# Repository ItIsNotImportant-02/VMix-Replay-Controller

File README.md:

# vMix Replay Controller

Vlastní hardwarový ovladač pro vMix Replay ve stylu EVS: RGB tlačítka, páka pro rychlost, jog kolečko. Vlastní PCB (KiCad, osazení JLCPCB), vlastní firmware, 3D tištěná krabička.

- Plán projektu: [docs/PLAN.md](docs/PLAN.md)
- Dashboard postupu: https://claude.ai/artifact/F6eHfhQ5NSxDFNfWmzDA3g
- Deep Research prompty: [docs/research/](docs/research/)

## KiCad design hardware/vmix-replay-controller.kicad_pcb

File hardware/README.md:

# Hardware (KiCad 9)

Hlavní deska ovladače. Popis návrhu a otevřené body: [DESIGN.md](DESIGN.md), piny a mapování tlačítek/LED: [PINMAP.md](PINMAP.md).

- `vmix-replay-controller.kicad_pro` a `vmix-replay-controller.kicad_sch`: projekt a jednostránkové blokové schéma (generované z `tools/circuit.py` + `tools/layout.py`, needitovat ručně)
- `lib/`: vlastní symboly a footprinty (PB26, TS5, IS31FL3236A QFN-44)
- `tools/`: generátor schématu a footprintů (`gen.py`), kontrola netlistu (`verify.py`), rozmístění desky ze schématu (`pcb.py`) a export BOM + CPL pro JLCPCB (`jlc.py`)
- `production/`: výrobní data pro JLCPCB (Gerber, BOM, CPL), doplní se po návrhu desky

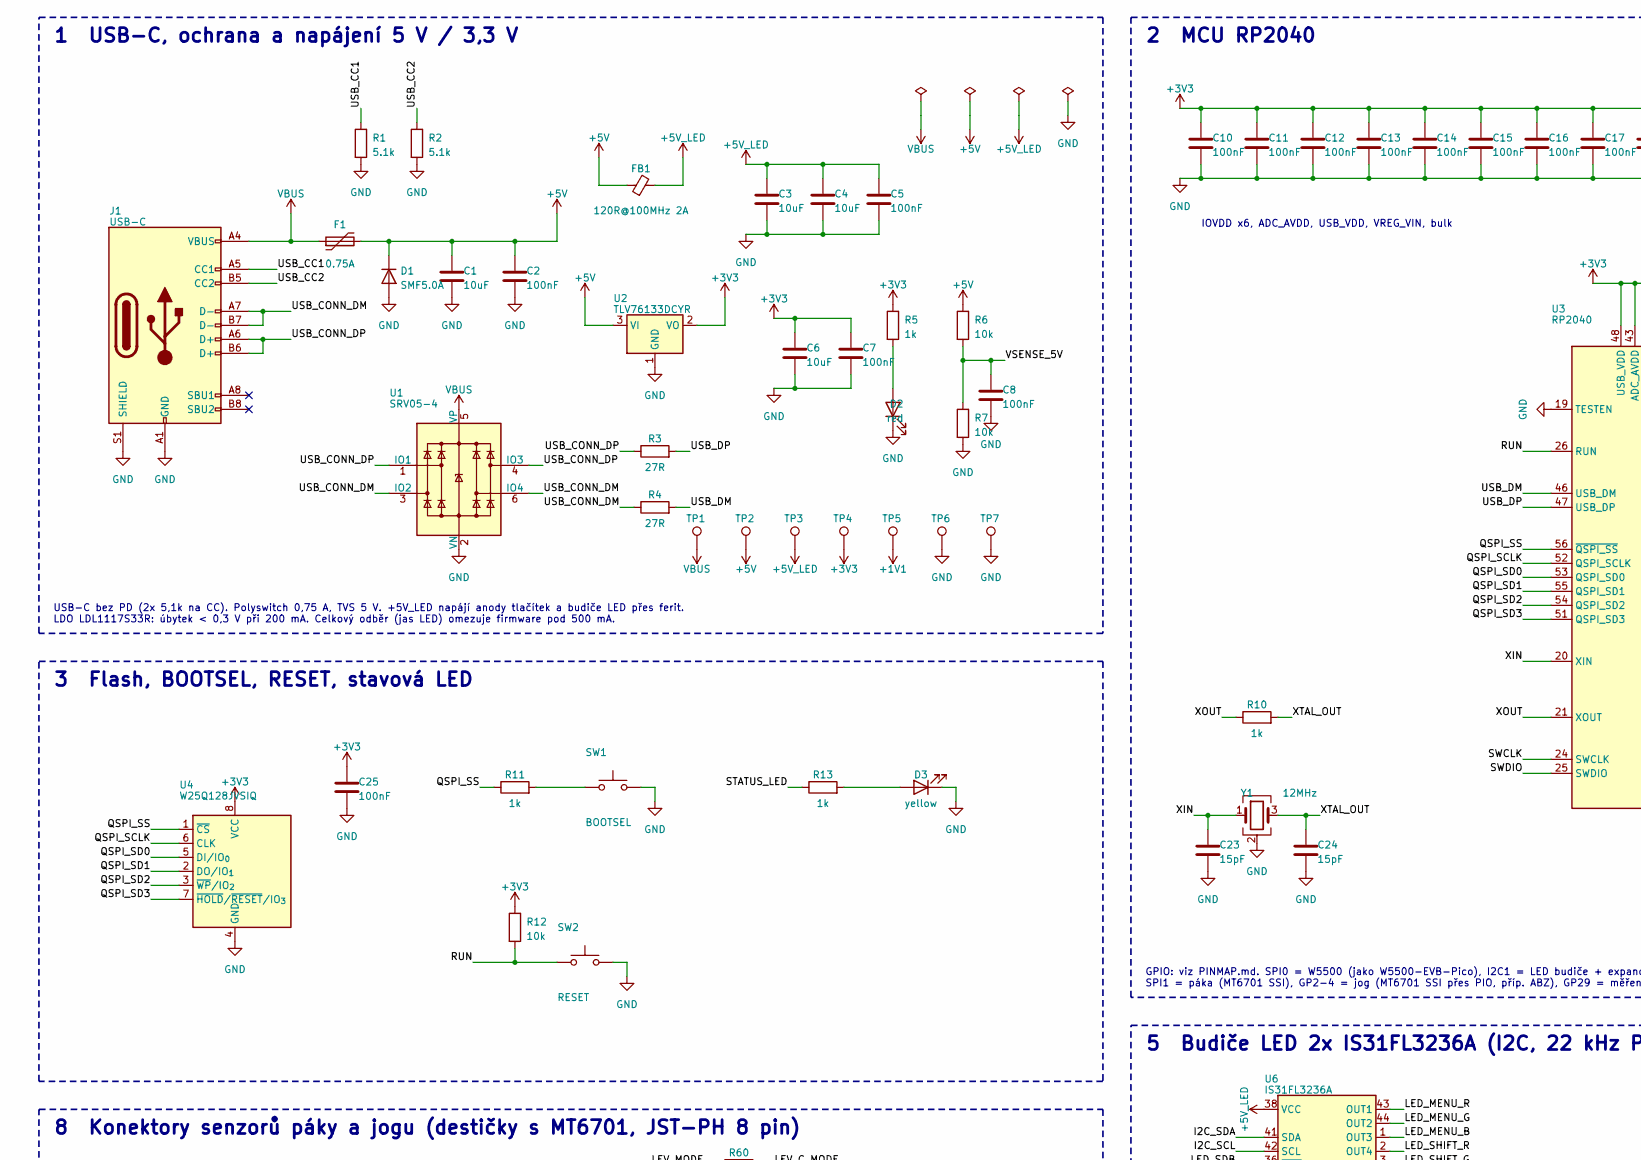
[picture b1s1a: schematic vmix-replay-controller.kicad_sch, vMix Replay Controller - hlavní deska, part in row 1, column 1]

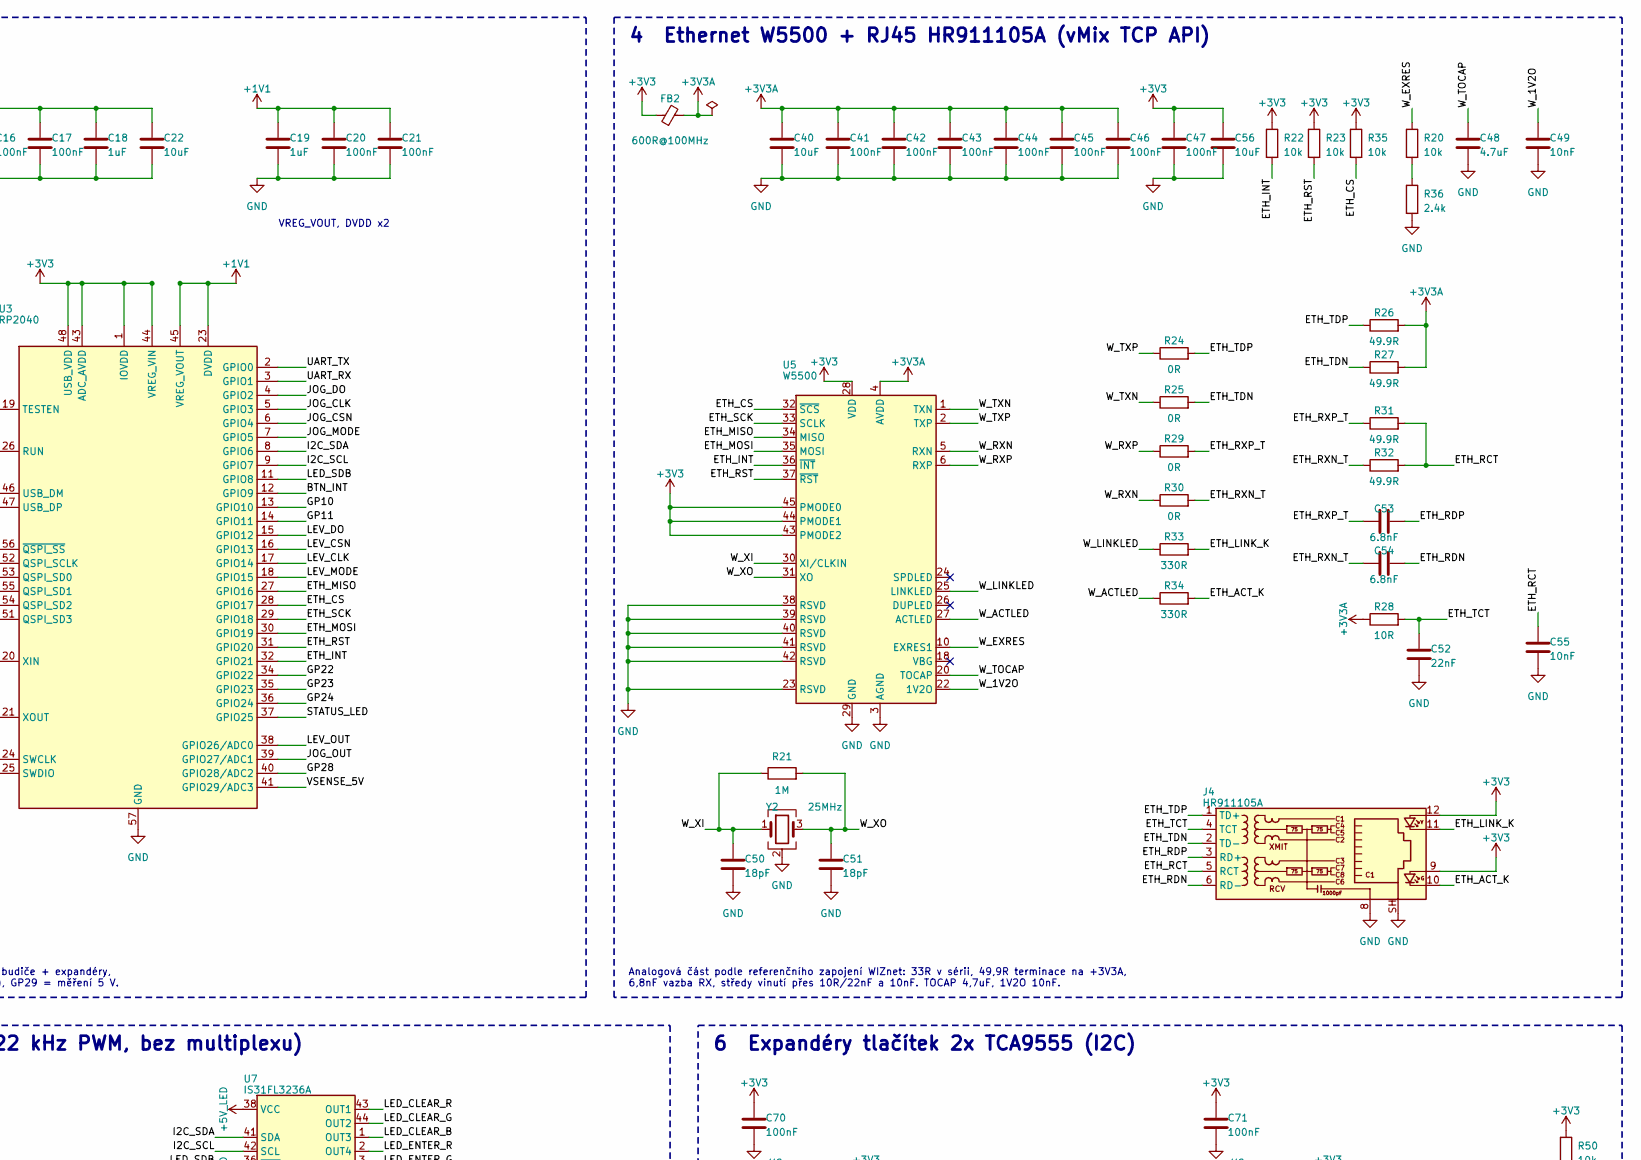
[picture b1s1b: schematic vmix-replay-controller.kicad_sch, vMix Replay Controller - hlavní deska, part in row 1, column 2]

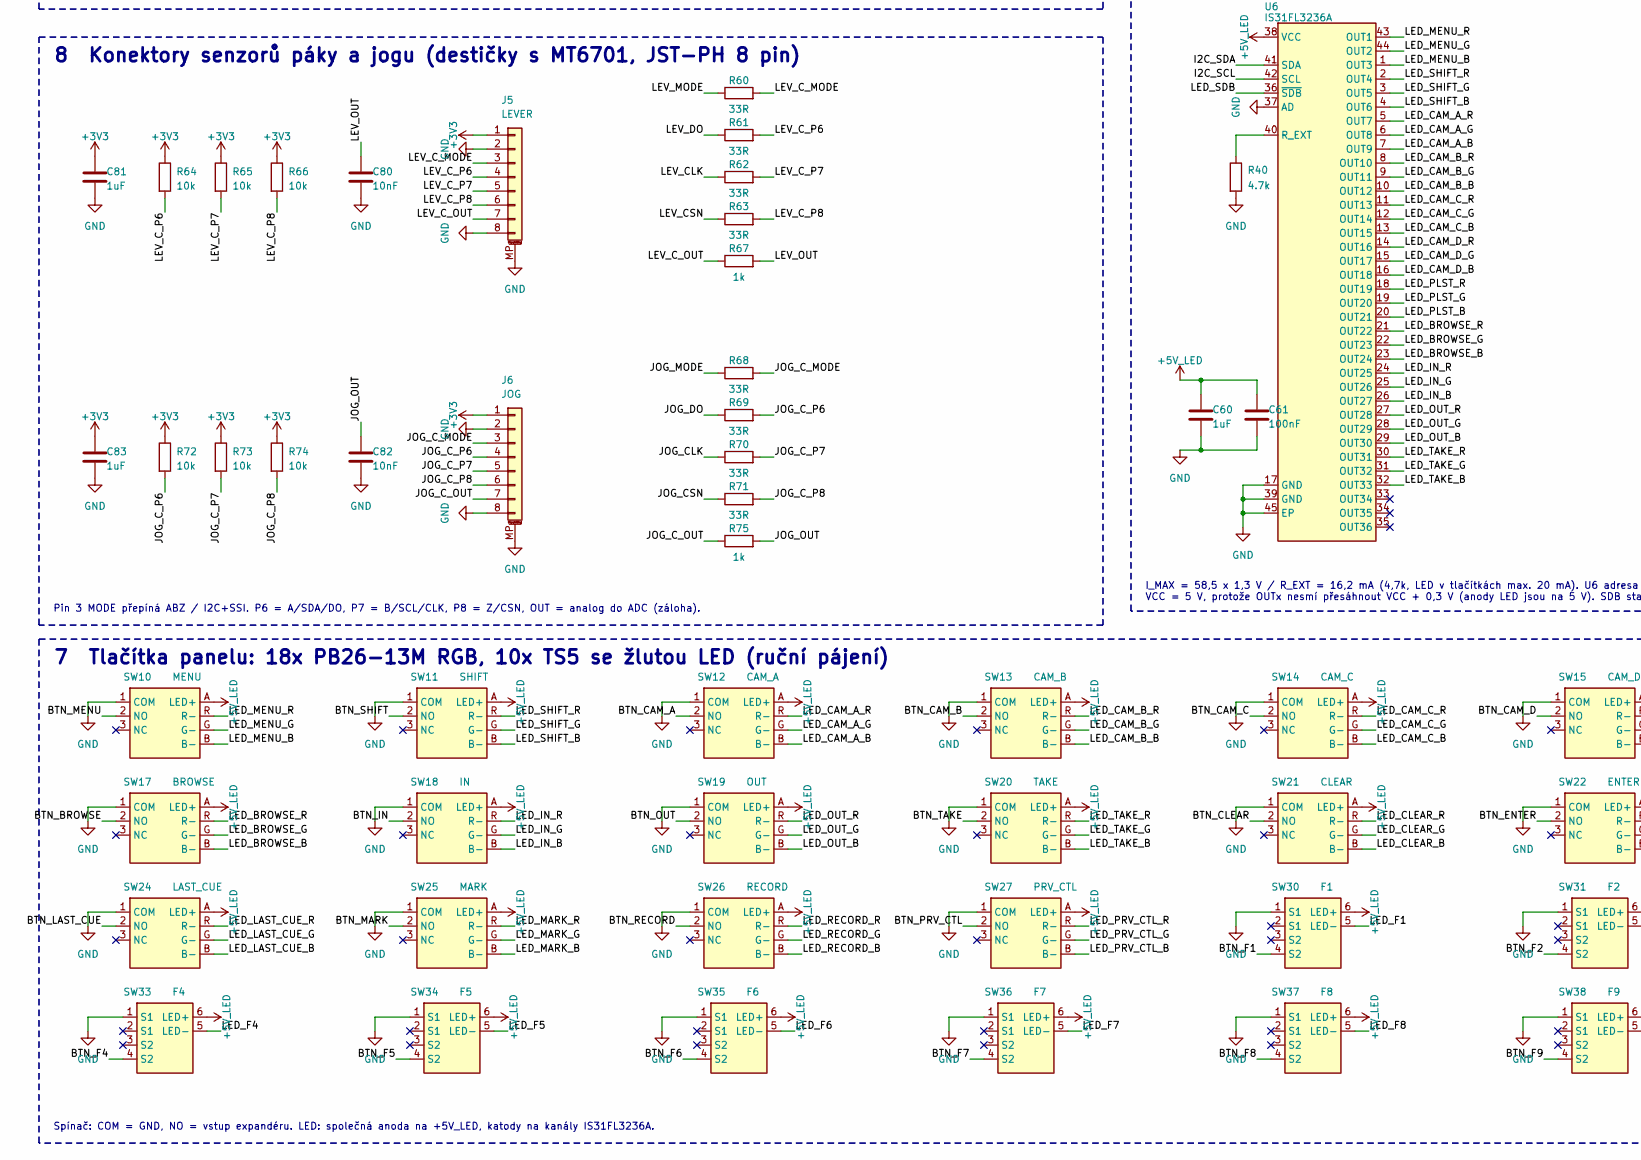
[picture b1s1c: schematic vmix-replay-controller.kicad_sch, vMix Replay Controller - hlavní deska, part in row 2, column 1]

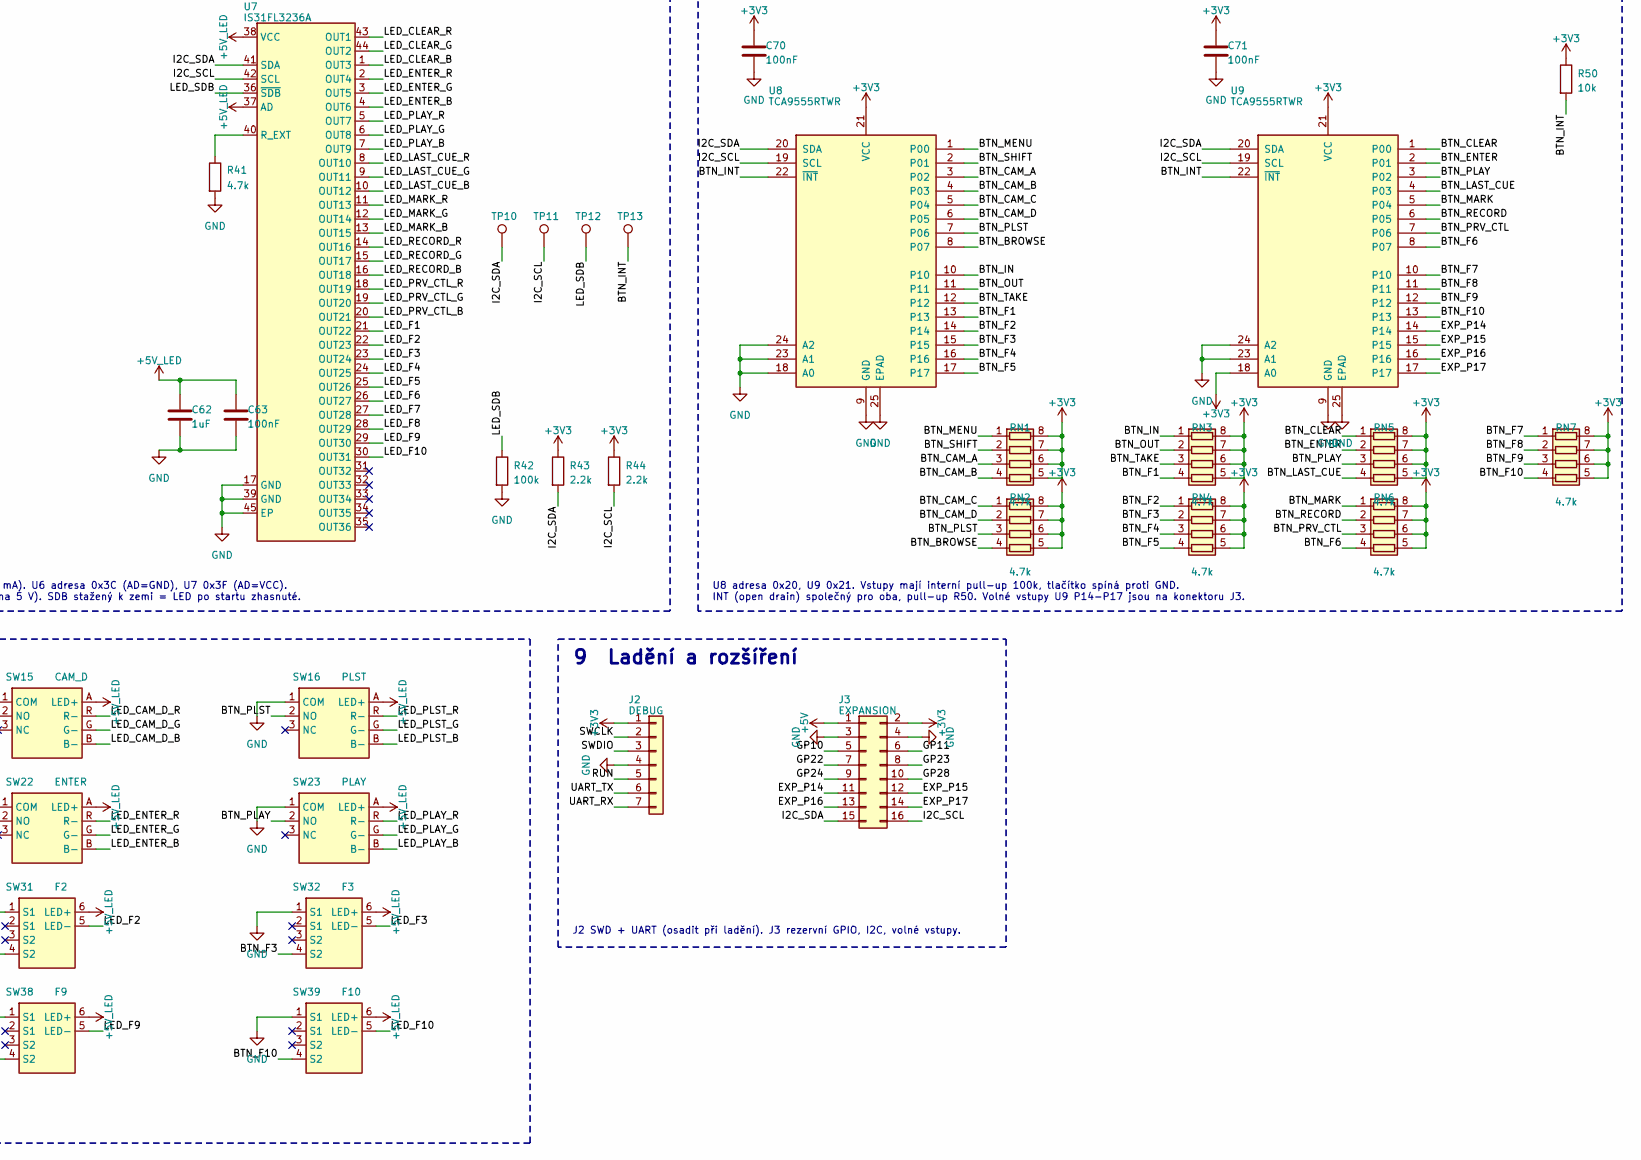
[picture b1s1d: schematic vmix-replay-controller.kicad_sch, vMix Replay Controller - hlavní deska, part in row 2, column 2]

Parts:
C1, C3, C4, C6, C22, C40, C56: 10uF; C_0805_2012Metric; LCSC C15850
C2, C5, C7, C8, C10, C11, C12, C13, C14, C15, C16, C17, C20, C21, C25, C41, C42, C43, C44, C45, C46, C47, C61, C63, C70, C71: 100nF; C_0603_1608Metric; LCSC C14663
C18, C19, C60, C62, C81, C83: 1uF; C_0603_1608Metric; LCSC C15849
C23, C24: 15pF; C_0603_1608Metric; LCSC C1644
C48: 4.7uF; C_0603_1608Metric; LCSC C19666
C49, C55, C80, C82: 10nF; C_0603_1608Metric; LCSC C57112
C50, C51: 18pF; C_0603_1608Metric; LCSC C1647
C52: 22nF; C_0603_1608Metric; LCSC C21122
C53, C54: 6.8nF; C_0603_1608Metric; LCSC C1631
D1: SMF5.0A; D_SOD-123F; MPN hongjiacheng SMF5.0A; LCSC C19077497
D2: red; LED_0603_1608Metric; MPN KENTO KT-0603R; LCSC C2286
D3: yellow; LED_0603_1608Metric; MPN NationStar NCD0603Y2; LCSC C89811
F1: 0.75A; Fuse_1206_3216Metric; MPN JK-nSMD075/6V; LCSC C2830242
FB1: 120R@100MHz 2A; L_0603_1608Metric; MPN BLM18PG121SN1D; LCSC C14709
FB2: 600R@100MHz; L_0805_2012Metric; LCSC C1017
J1: USB-C; USB_C_Receptacle_HRO_TYPE-C-31-M-12; MPN TYPE-C-31-M-12; LCSC C165948
J2: DEBUG; PinHeader_1x07_P2.54mm_Vertical
J3: EXPANSION; PinHeader_2x08_P2.54mm_Vertical
J4: HR911105A; RJ45_Hanrun_HR911105A_Horizontal; LCSC C12074
J5: LEVER; JST_PH_S8B-PH-SM4-TB_1x08-1MP_P2.00mm_Horizontal; MPN S8B-PH-SM4-TB; LCSC C265121
J6: JOG; JST_PH_S8B-PH-SM4-TB_1x08-1MP_P2.00mm_Horizontal; MPN S8B-PH-SM4-TB; LCSC C265121
R1, R2: 5.1k; R_0603_1608Metric; Tolerance 1%; LCSC C23186
R3, R4: 27R; R_0603_1608Metric; Tolerance 1%; LCSC C25190
R5, R10, R11, R13, R67, R75: 1k; R_0603_1608Metric; Tolerance 1%; LCSC C21190
R6, R7, R12, R20, R22, R23, R35, R50, R64, R65, R66, R72, R73, R74: 10k; R_0603_1608Metric; Tolerance 1%; LCSC C25804
R21: 1M; R_0603_1608Metric; Tolerance 1%; LCSC C22935
R24, R25, R29, R30: 0R; R_0603_1608Metric; Tolerance 1%; LCSC C21189
R26, R27, R31, R32: 49.9R; R_0603_1608Metric; Tolerance 1%; LCSC C23185
R28: 10R; R_0603_1608Metric; Tolerance 1%; LCSC C22859
R33, R34: 330R; R_0603_1608Metric; Tolerance 1%; LCSC C23138
R36: 2.4k; R_0603_1608Metric; Tolerance 1%; LCSC C22940
R40, R41: 4.7k; R_0603_1608Metric; Tolerance 1%; LCSC C23162
R42: 100k; R_0603_1608Metric; Tolerance 1%; LCSC C25803
R43, R44: 2.2k; R_0603_1608Metric; Tolerance 1%; LCSC C4190
R60, R61, R62, R63, R68, R69, R70, R71: 33R; R_0603_1608Metric; Tolerance 1%; LCSC C23140
RN1, RN2, RN3, RN4, RN5, RN6, RN7: 4.7k; R_Array_Convex_4x0603; MPN 4D03WGJ0472T5E; LCSC C1980
SW1: BOOTSEL; SW_Push_1P1T_XKB_TS-1187A; LCSC C318884
SW2: RESET; SW_Push_1P1T_XKB_TS-1187A; LCSC C318884
SW10: MENU; PB26-13M-RGB; MPN PB26-13M-B-WT-RGB-N
SW11: SHIFT; PB26-13M-RGB; MPN PB26-13M-B-WT-RGB-N
SW12: CAM_A; PB26-13M-RGB; MPN PB26-13M-B-WT-RGB-N
SW13: CAM_B; PB26-13M-RGB; MPN PB26-13M-B-WT-RGB-N
SW14: CAM_C; PB26-13M-RGB; MPN PB26-13M-B-WT-RGB-N
SW15: CAM_D; PB26-13M-RGB; MPN PB26-13M-B-WT-RGB-N
SW16: PLST; PB26-13M-RGB; MPN PB26-13M-B-WT-RGB-N
SW17: BROWSE; PB26-13M-RGB; MPN PB26-13M-B-WT-RGB-N
SW18: IN; PB26-13M-RGB; MPN PB26-13M-B-WT-RGB-N
SW19: OUT; PB26-13M-RGB; MPN PB26-13M-B-WT-RGB-N
SW20: TAKE; PB26-13M-RGB; MPN PB26-13M-B-WT-RGB-N
SW21: CLEAR; PB26-13M-RGB; MPN PB26-13M-B-WT-RGB-N
SW22: ENTER; PB26-13M-RGB; MPN PB26-13M-B-WT-RGB-N
SW23: PLAY; PB26-13M-RGB; MPN PB26-13M-B-WT-RGB-N
SW24: LAST_CUE; PB26-13M-RGB; MPN PB26-13M-B-WT-RGB-N
SW25: MARK; PB26-13M-RGB; MPN PB26-13M-B-WT-RGB-N
SW26: RECORD; PB26-13M-RGB; MPN PB26-13M-B-WT-RGB-N
SW27: PRV_CTL; PB26-13M-RGB; MPN PB26-13M-B-WT-RGB-N
SW30: F1; TS5-9.2mm-LED; MPN TS5 yellow
SW31: F2; TS5-9.2mm-LED; MPN TS5 yellow
SW32: F3; TS5-9.2mm-LED; MPN TS5 yellow
SW33: F4; TS5-9.2mm-LED; MPN TS5 yellow
SW34: F5; TS5-9.2mm-LED; MPN TS5 yellow
SW35: F6; TS5-9.2mm-LED; MPN TS5 yellow
SW36: F7; TS5-9.2mm-LED; MPN TS5 yellow
SW37: F8; TS5-9.2mm-LED; MPN TS5 yellow
SW38: F9; TS5-9.2mm-LED; MPN TS5 yellow
SW39: F10; TS5-9.2mm-LED; MPN TS5 yellow
TP1: VBUS; TestPoint_Pad_D1.5mm
TP2: +5V; TestPoint_Pad_D1.5mm
TP3: +5V_LED; TestPoint_Pad_D1.5mm
TP4: +3V3; TestPoint_Pad_D1.5mm
TP5: +1V1; TestPoint_Pad_D1.5mm
TP6, TP7: GND; TestPoint_Pad_D1.5mm
TP10: I2C_SDA; TestPoint_Pad_D1.5mm
TP11: I2C_SCL; TestPoint_Pad_D1.5mm
TP12: LED_SDB; TestPoint_Pad_D1.5mm
TP13: BTN_INT; TestPoint_Pad_D1.5mm
U1: SRV05-4; SOT-23-6; MPN hongjiacheng SRV05-4; LCSC C7420376
U2: TLV76133DCYR; SOT-223-3_TabPin2; MPN TLV76133DCYR; LCSC C7527500
U3: RP2040; QFN-56-1EP_7x7mm_P0.4mm_EP3.2x3.2mm; LCSC C2040
U4: W25Q128JVSIQ; SOIC-8_5.3x5.3mm_P1.27mm; LCSC C97521
U5: W5500; LQFP-48_7x7mm_P0.5mm; LCSC C32843
U6, U7: IS31FL3236A; QFN-44-1EP_5x5mm_P0.4mm; MPN IS31FL3236A-QFLS2-TR; LCSC C246443
U8, U9: TCA9555RTWR; Texas_RTW_WQFN-24-1EP_4x4mm_P0.5mm_EP2.7x2.7mm; LCSC C140277
Y1: 12MHz; Crystal_SMD_3225-4Pin_3.2x2.5mm; MPN TX322512M4DBDE2T; LCSC C5310728
Y2: 25MHz; Crystal_SMD_3225-4Pin_3.2x2.5mm; MPN X322525MOB4SI (CL 12 pF); LCSC C9006

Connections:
+1V1: C19.1, C20.1, C21.1, TP5.1, U3.23 (DVDD), U3.45 (VREG_VOUT), U3.50 (DVDD)
+3V3: C6.1, C7.1, C10.1, C11.1, C12.1, C13.1, C14.1, C15.1, C16.1, C17.1, C18.1, C22.1, C25.1, C47.1, C56.1, C70.1, C71.1, C81.1, C83.1, FB2.1, J2.1, J3.2, J4.9, J4.12, J5.1, J6.1, R5.1, R12.1, R22.1, R23.1, R35.1, R43.1, R44.1, R50.1, R64.1, R65.1, R66.1, R72.1, R73.1, R74.1, RN1.5 (R4.2), RN1.6 (R3.2), RN1.7 (R2.2), RN1.8 (R1.2), RN2.5 (R4.2), RN2.6 (R3.2), RN2.7 (R2.2), RN2.8 (R1.2), RN3.5 (R4.2), RN3.6 (R3.2), RN3.7 (R2.2), RN3.8 (R1.2), RN4.5 (R4.2), RN4.6 (R3.2), RN4.7 (R2.2), RN4.8 (R1.2), RN5.5 (R4.2), RN5.6 (R3.2), RN5.7 (R2.2), RN5.8 (R1.2), RN6.5 (R4.2), RN6.6 (R3.2), RN6.7 (R2.2), RN6.8 (R1.2), RN7.5 (R4.2), RN7.6 (R3.2), RN7.7 (R2.2), RN7.8 (R1.2), TP4.1, U2.2 (VO), U3.1 (IOVDD), U3.10 (IOVDD), U3.22 (IOVDD), U3.33 (IOVDD), U3.42 (IOVDD), U3.43 (ADC_AVDD), U3.44 (VREG_VIN), U3.48 (USB_VDD), U3.49 (IOVDD), U4.8 (VCC), U5.28 (VDD), U5.43 (PMODE2), U5.44 (PMODE1), U5.45 (PMODE0), U8.21 (VCC), U9.18 (A0), U9.21 (VCC)
+3V3A: C40.1, C41.1, C42.1, C43.1, C44.1, C45.1, C46.1, FB2.2, R26.2, R27.2, R28.1, U5.4 (AVDD), U5.8 (AVDD), U5.11 (AVDD), U5.15 (AVDD), U5.17 (AVDD), U5.21 (AVDD)
+5V: C1.1, C2.1, D1.1 (K), F1.2, FB1.1, J3.1, R6.1, TP2.1, U2.3 (VI)
+5V_LED: C3.1, C4.1, C5.1, C60.1, C61.1, C62.1, C63.1, FB1.2, SW10.A (LED+), SW11.A (LED+), SW12.A (LED+), SW13.A (LED+), SW14.A (LED+), SW15.A (LED+), SW16.A (LED+), SW17.A (LED+), SW18.A (LED+), SW19.A (LED+), SW20.A (LED+), SW21.A (LED+), SW22.A (LED+), SW23.A (LED+), SW24.A (LED+), SW25.A (LED+), SW26.A (LED+), SW27.A (LED+), SW30.6 (LED+), SW31.6 (LED+), SW32.6 (LED+), SW33.6 (LED+), SW34.6 (LED+), SW35.6 (LED+), SW36.6 (LED+), SW37.6 (LED+), SW38.6 (LED+), SW39.6 (LED+), TP3.1, U6.38 (VCC), U7.37 (AD), U7.38 (VCC)
/BTN_BROWSE: RN2.4 (R4.1), SW17.2 (NO), U8.8 (P07)
/BTN_CAM_A: RN1.3 (R3.1), SW12.2 (NO), U8.3 (P02)
/BTN_CAM_B: RN1.4 (R4.1), SW13.2 (NO), U8.4 (P03)
/BTN_CAM_C: RN2.1 (R1.1), SW14.2 (NO), U8.5 (P04)
/BTN_CAM_D: RN2.2 (R2.1), SW15.2 (NO), U8.6 (P05)
/BTN_CLEAR: RN5.1 (R1.1), SW21.2 (NO), U9.1 (P00)
/BTN_ENTER: RN5.2 (R2.1), SW22.2 (NO), U9.2 (P01)
/BTN_F1: RN3.4 (R4.1), SW30.4 (S2), U8.13
/BTN_F2: RN4.1 (R1.1), SW31.4 (S2), U8.14
/BTN_F3: RN4.2 (R2.1), SW32.4 (S2), U8.15
/BTN_F4: RN4.3 (R3.1), SW33.4 (S2), U8.16
/BTN_F5: RN4.4 (R4.1), SW34.4 (S2), U8.17
/BTN_F6: RN6.4 (R4.1), SW35.4 (S2), U9.8 (P07)
/BTN_F7: RN7.1 (R1.1), SW36.4 (S2), U9.10
/BTN_F8: RN7.2 (R2.1), SW37.4 (S2), U9.11
/BTN_F9: RN7.3 (R3.1), SW38.4 (S2), U9.12
/BTN_F10: RN7.4 (R4.1), SW39.4 (S2), U9.13
/BTN_IN: RN3.1 (R1.1), SW18.2 (NO), U8.10
/BTN_INT: R50.2, TP13.1, U3.12 (GPIO9), U8.22 (~INT), U9.22 (~INT)
/BTN_LAST_CUE: RN5.4 (R4.1), SW24.2 (NO), U9.4 (P03)
/BTN_MARK: RN6.1 (R1.1), SW25.2 (NO), U9.5 (P04)
/BTN_MENU: RN1.1 (R1.1), SW10.2 (NO), U8.1 (P00)
/BTN_OUT: RN3.2 (R2.1), SW19.2 (NO), U8.11
/BTN_PLAY: RN5.3 (R3.1), SW23.2 (NO), U9.3 (P02)
/BTN_PLST: RN2.3 (R3.1), SW16.2 (NO), U8.7 (P06)
/BTN_PRV_CTL: RN6.3 (R3.1), SW27.2 (NO), U9.7 (P06)
/BTN_RECORD: RN6.2 (R2.1), SW26.2 (NO), U9.6 (P05)
/BTN_SHIFT: RN1.2 (R2.1), SW11.2 (NO), U8.2 (P01)
/BTN_TAKE: RN3.3 (R3.1), SW20.2 (NO), U8.12
/ETH_ACT_K: J4.10, R34.2
/ETH_CS: R35.2, U3.28 (GPIO17), U5.32 (~SCS)
/ETH_INT: R22.2, U3.32 (GPIO21), U5.36 (~INT)
/ETH_LINK_K: J4.11, R33.2
/ETH_MISO: U3.27 (GPIO16), U5.34 (MISO)
/ETH_MOSI: U3.30 (GPIO19), U5.35 (MOSI)
/ETH_RCT: C55.1, J4.5 (RCT), R31.2, R32.2
/ETH_RDN: C54.2, J4.6 (RD-)
/ETH_RDP: C53.2, J4.3 (RD+)
/ETH_RST: R23.2, U3.31 (GPIO20), U5.37 (~RST)
/ETH_RXN_T: C54.1, R30.2, R32.1
/ETH_RXP_T: C53.1, R29.2, R31.1
/ETH_SCK: U3.29 (GPIO18), U5.33 (SCLK)
/ETH_TCT: C52.1, J4.4 (TCT), R28.2
/ETH_TDN: J4.2 (TD-), R25.2, R27.1
/ETH_TDP: J4.1 (TD+), R24.2, R26.1
/EXP_P14: J3.11, U9.14
/EXP_P15: J3.12, U9.15
/EXP_P16: J3.13, U9.16
/EXP_P17: J3.14, U9.17
/GP10: J3.5, U3.13 (GPIO10)
/GP11: J3.6, U3.14 (GPIO11)
/GP22: J3.7, U3.34 (GPIO22)
/GP23: J3.8, U3.35 (GPIO23)
/GP24: J3.9, U3.36 (GPIO24)
/GP28: J3.10, U3.40 (GPIO28/ADC2)
/I2C_SCL: J3.16, R44.2, TP11.1, U3.9 (GPIO7), U6.42 (SCL), U7.42 (SCL), U8.19 (SCL), U9.19 (SCL)
/I2C_SDA: J3.15, R43.2, TP10.1, U3.8 (GPIO6), U6.41 (SDA), U7.41 (SDA), U8.20 (SDA), U9.20 (SDA)
/JOG_CLK: R70.1, U3.5 (GPIO3)
/JOG_CSN: R71.1, U3.6 (GPIO4)
/JOG_C_MODE: J6.3, R68.2
/JOG_C_OUT: J6.7, R75.1
/JOG_C_P6: J6.4, R69.2, R72.2
/JOG_C_P7: J6.5, R70.2, R73.2
/JOG_C_P8: J6.6, R71.2, R74.2
/JOG_DO: R69.1, U3.4 (GPIO2)
/JOG_MODE: R68.1, U3.7 (GPIO5)
/JOG_OUT: C82.1, R75.2, U3.39 (GPIO27/ADC1)
/LED_BROWSE_B: SW17.B (B-), U6.23 (OUT24)
/LED_BROWSE_G: SW17.G (G-), U6.22 (OUT23)
/LED_BROWSE_R: SW17.R (R-), U6.21 (OUT22)
/LED_CAM_A_B: SW12.B (B-), U6.7 (OUT9)
/LED_CAM_A_G: SW12.G (G-), U6.6 (OUT8)
/LED_CAM_A_R: SW12.R (R-), U6.5 (OUT7)
/LED_CAM_B_B: SW13.B (B-), U6.10 (OUT12)
/LED_CAM_B_G: SW13.G (G-), U6.9 (OUT11)
/LED_CAM_B_R: SW13.R (R-), U6.8 (OUT10)
/LED_CAM_C_B: SW14.B (B-), U6.13 (OUT15)
/LED_CAM_C_G: SW14.G (G-), U6.12 (OUT14)
/LED_CAM_C_R: SW14.R (R-), U6.11 (OUT13)
/LED_CAM_D_B: SW15.B (B-), U6.16 (OUT18)
/LED_CAM_D_G: SW15.G (G-), U6.15 (OUT17)
/LED_CAM_D_R: SW15.R (R-), U6.14 (OUT16)
/LED_CLEAR_B: SW21.B (B-), U7.1 (OUT3)
/LED_CLEAR_G: SW21.G (G-), U7.44 (OUT2)
/LED_CLEAR_R: SW21.R (R-), U7.43 (OUT1)
/LED_ENTER_B: SW22.B (B-), U7.4 (OUT6)
/LED_ENTER_G: SW22.G (G-), U7.3 (OUT5)
/LED_ENTER_R: SW22.R (R-), U7.2 (OUT4)
/LED_F1: SW30.5 (LED-), U7.21 (OUT22)
/LED_F2: SW31.5 (LED-), U7.22 (OUT23)
/LED_F3: SW32.5 (LED-), U7.23 (OUT24)
/LED_F4: SW33.5 (LED-), U7.24 (OUT25)
/LED_F5: SW34.5 (LED-), U7.25 (OUT26)
/LED_F6: SW35.5 (LED-), U7.26 (OUT27)
/LED_F7: SW36.5 (LED-), U7.27 (OUT28)
/LED_F8: SW37.5 (LED-), U7.28 (OUT29)
/LED_F9: SW38.5 (LED-), U7.29 (OUT30)
/LED_F10: SW39.5 (LED-), U7.30 (OUT31)
/LED_IN_B: SW18.B (B-), U6.26 (OUT27)
/LED_IN_G: SW18.G (G-), U6.25 (OUT26)
/LED_IN_R: SW18.R (R-), U6.24 (OUT25)
/LED_LAST_CUE_B: SW24.B (B-), U7.10 (OUT12)
/LED_LAST_CUE_G: SW24.G (G-), U7.9 (OUT11)
/LED_LAST_CUE_R: SW24.R (R-), U7.8 (OUT10)
/LED_MARK_B: SW25.B (B-), U7.13 (OUT15)
/LED_MARK_G: SW25.G (G-), U7.12 (OUT14)
/LED_MARK_R: SW25.R (R-), U7.11 (OUT13)
/LED_MENU_B: SW10.B (B-), U6.1 (OUT3)
/LED_MENU_G: SW10.G (G-), U6.44 (OUT2)
/LED_MENU_R: SW10.R (R-), U6.43 (OUT1)
/LED_OUT_B: SW19.B (B-), U6.29 (OUT30)
/LED_OUT_G: SW19.G (G-), U6.28 (OUT29)
/LED_OUT_R: SW19.R (R-), U6.27 (OUT28)
/LED_PLAY_B: SW23.B (B-), U7.7 (OUT9)
/LED_PLAY_G: SW23.G (G-), U7.6 (OUT8)
/LED_PLAY_R: SW23.R (R-), U7.5 (OUT7)
/LED_PLST_B: SW16.B (B-), U6.20 (OUT21)
/LED_PLST_G: SW16.G (G-), U6.19 (OUT20)
/LED_PLST_R: SW16.R (R-), U6.18 (OUT19)
/LED_PRV_CTL_B: SW27.B (B-), U7.20 (OUT21)
/LED_PRV_CTL_G: SW27.G (G-), U7.19 (OUT20)
/LED_PRV_CTL_R: SW27.R (R-), U7.18 (OUT19)
/LED_RECORD_B: SW26.B (B-), U7.16 (OUT18)
/LED_RECORD_G: SW26.G (G-), U7.15 (OUT17)
/LED_RECORD_R: SW26.R (R-), U7.14 (OUT16)
/LED_SDB: R42.1, TP12.1, U3.11 (GPIO8), U6.36 (~SDB), U7.36 (~SDB)
/LED_SHIFT_B: SW11.B (B-), U6.4 (OUT6)
/LED_SHIFT_G: SW11.G (G-), U6.3 (OUT5)
/LED_SHIFT_R: SW11.R (R-), U6.2 (OUT4)
/LED_TAKE_B: SW20.B (B-), U6.32 (OUT33)
/LED_TAKE_G: SW20.G (G-), U6.31 (OUT32)
/LED_TAKE_R: SW20.R (R-), U6.30 (OUT31)
/LEV_CLK: R62.1, U3.17 (GPIO14)
/LEV_CSN: R63.1, U3.16 (GPIO13)
/LEV_C_MODE: J5.3, R60.2
/LEV_C_OUT: J5.7, R67.1
/LEV_C_P6: J5.4, R61.2, R64.2
/LEV_C_P7: J5.5, R62.2, R65.2
/LEV_C_P8: J5.6, R63.2, R66.2
/LEV_DO: R61.1, U3.15 (GPIO12)
/LEV_MODE: R60.1, U3.18 (GPIO15)
/LEV_OUT: C80.1, R67.2, U3.38 (GPIO26/ADC0)
/QSPI_SCLK: U3.52 (QSPI_SCLK), U4.6 (CLK)
/QSPI_SD0: U3.53 (QSPI_SD0), U4.5 (DI/IO_{0})
/QSPI_SD1: U3.55 (QSPI_SD1), U4.2 (DO/IO_{1})
/QSPI_SD2: U3.54 (QSPI_SD2), U4.3 (~WP/IO_{2})
/QSPI_SD3: U3.51 (QSPI_SD3), U4.7 (~HOLD/~RESET/IO_{3})
/QSPI_SS: R11.1, U3.56 (~QSPI_SS), U4.1 (~CS)
/RUN: J2.5, R12.2, SW2.1, U3.26 (RUN)
/STATUS_LED: R13.1, U3.37 (GPIO25)
/SWCLK: J2.2, U3.24 (SWCLK)
/SWDIO: J2.3, U3.25 (SWDIO)
/UART_RX: J2.7, U3.3 (GPIO1)
/UART_TX: J2.6, U3.2 (GPIO0)
/USB_CC1: J1.A5 (CC1), R1.1
/USB_CC2: J1.B5 (CC2), R2.1
/USB_CONN_DM: J1.A7 (D-), J1.B7 (D-), R4.1, U1.3 (IO2), U1.6 (IO4)
/USB_CONN_DP: J1.A6 (D+), J1.B6 (D+), R3.1, U1.1 (IO1), U1.4 (IO3)
/USB_DM: R4.2, U3.46 (USB_DM)
/USB_DP: R3.2, U3.47 (USB_DP)
/VSENSE_5V: C8.1, R6.2, R7.1, U3.41 (GPIO29/ADC3)
/W_1V2O: C49.1, U5.22 (1V2O)
/W_ACTLED: R34.1, U5.27 (ACTLED)
/W_EXRES: R20.1, U5.10 (EXRES1)
/W_LINKLED: R33.1, U5.25 (LINKLED)
/W_RXN: R30.1, U5.5 (RXN)
/W_RXP: R29.1, U5.6 (RXP)
/W_TOCAP: C48.1, U5.20 (TOCAP)
/W_TXN: R25.1, U5.1 (TXN)
/W_TXP: R24.1, U5.2 (TXP)
/W_XI: C50.1, R21.1, U5.30 (XI/CLKIN), Y2.1
/W_XO: C51.1, R21.2, U5.31 (XO), Y2.3
/XIN: C23.1, U3.20 (XIN), Y1.1
/XOUT: R10.1, U3.21 (XOUT)
/XTAL_OUT: C24.1, R10.2, Y1.3
GND: C1.2, C2.2, C3.2, C4.2, C5.2, C6.2, C7.2, C8.2, C10.2, C11.2, C12.2, C13.2, C14.2, C15.2, C16.2, C17.2, C18.2, C19.2, C20.2, C21.2, C22.2, C23.2, C24.2, C25.2, C40.2, C41.2, C42.2, C43.2, C44.2, C45.2, C46.2, C47.2, C48.2, C49.2, C50.2, C51.2, C52.2, C55.2, C56.2, C60.2, C61.2, C62.2, C63.2, C70.2, C71.2, C80.2, C81.2, C82.2, C83.2, D1.2 (A), D2.1 (K), D3.1 (K), J1.A1 (GND), J1.A12 (GND), J1.B1 (GND), J1.B12 (GND), J1.S1 (SHIELD), J2.4, J3.3, J3.4, J4.8, J4.SH, J5.2, J5.8, J5.MP (MountPin), J6.2, J6.8, J6.MP (MountPin), R1.2, R2.2, R7.2, R36.2, R40.2, R41.2, R42.2, SW1.2, SW2.2, SW10.1 (COM), SW11.1 (COM), SW12.1 (COM), SW13.1 (COM), SW14.1 (COM), SW15.1 (COM), SW16.1 (COM), SW17.1 (COM), SW18.1 (COM), SW19.1 (COM), SW20.1 (COM), SW21.1 (COM), SW22.1 (COM), SW23.1 (COM), SW24.1 (COM), SW25.1 (COM), SW26.1 (COM), SW27.1 (COM), SW30.1 (S1), SW31.1 (S1), SW32.1 (S1), SW33.1 (S1), SW34.1 (S1), SW35.1 (S1), SW36.1 (S1), SW37.1 (S1), SW38.1 (S1), SW39.1 (S1), TP6.1, TP7.1, U1.2 (VN), U2.1 (GND), U3.19 (TESTEN), U3.57 (GND), U4.4 (GND), U5.3 (AGND), U5.9 (AGND), U5.14 (AGND), U5.16 (AGND), U5.19 (AGND), U5.23 (RSVD), U5.29 (GND), U5.38 (RSVD), U5.39 (RSVD), U5.40 (RSVD), U5.41 (RSVD), U5.42 (RSVD), U5.48 (AGND), U6.17 (GND), U6.37 (AD), U6.39 (GND), U6.45 (EP), U7.17 (GND), U7.39 (GND), U7.45 (EP), U8.9 (GND), U8.18 (A0), U8.23 (A1), U8.24 (A2), U8.25 (EPAD), U9.9 (GND), U9.23 (A1), U9.24 (A2), U9.25 (EPAD), Y1.2 (G), Y1.4 (G), Y2.2 (G), Y2.4 (G); also elsewhere on the board
unnamed: D2.2 (A), R5.2
unnamed: D3.2 (A), R13.2
unnamed: R11.2, SW1.1
unnamed: R20.2, R36.1
unnamed: R40.1, U6.40 (R_EXT)
unnamed: R41.1, U7.40 (R_EXT)
VBUS: F1.1, J1.A4 (VBUS), J1.A9 (VBUS), J1.B4 (VBUS), J1.B9 (VBUS), TP1.1, U1.5 (VP)

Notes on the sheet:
1 USB-C, ochrana a napájení 5 V / 3,3 V
USB-C bez PD (2x 5,1k na CC). Polyswitch 0,75 A, TVS 5 V. +5V_LED napájí anody tlačítek a budiče LED přes ferit. LDO LDL1117S33R: úbytek < 0,3 V při 200 mA. Celkový odběr (jas LED) omezuje firmware pod 500 mA.
2 MCU RP2040
GPIO: viz PINMAP.md. SPI0 = W5500 (jako W5500-EVB-Pico), I2C1 = LED budiče + expandéry, SPI1 = páka (MT6701 SSI), GP2-4 = jog (MT6701 SSI přes PIO, příp. ABZ), GP29 = měření 5 V.
IOVDD x6, ADC_AVDD, USB_VDD, VREG_VIN, bulk
VREG_VOUT, DVDD x2
4 Ethernet W5500 + RJ45 HR911105A (vMix TCP API)
Analogová část podle referenčního zapojení WIZnet: 33R v sérii, 49,9R terminace na +3V3A, 6,8nF vazba RX, středy vinutí přes 10R/22nF a 10nF. TOCAP 4,7uF, 1V2O 10nF.
3 Flash, BOOTSEL, RESET, stavová LED
5 Budiče LED 2x IS31FL3236A (I2C, 22 kHz PWM, bez multiplexu)
I_MAX = 58,5 x 1,3 V / R_EXT = 16,2 mA (4,7k, LED v tlačítkách max. 20 mA). U6 adresa 0x3C (AD=GND), U7 0x3F (AD=VCC). VCC = 5 V, protože OUTx nesmí přesáhnout VCC + 0,3 V (anody LED jsou na 5 V). SDB stažený k zemi = LED po startu zhasnuté.
6 Expandéry tlačítek 2x TCA9555 (I2C)
U8 adresa 0x20, U9 0x21. Vstupy mají interní pull-up 100k, tlačítko spíná proti GND. INT (open drain) společný pro oba, pull-up R50. Volné vstupy U9 P14-P17 jsou na konektoru J3.
7 Tlačítka panelu: 18x PB26-13M RGB, 10x TS5 se žlutou LED (ruční pájení)
Spínač: COM = GND, NO = vstup expandéru. LED: společná anoda na +5V_LED, katody na kanály IS31FL3236A.
8 Konektory senzorů páky a jogu (destičky s MT6701, JST-PH 8 pin)
Pin 3 MODE přepíná ABZ / I2C+SSI. P6 = A/SDA/DO, P7 = B/SCL/CLK, P8 = Z/CSN, OUT = analog do ADC (záloha).
9 Ladění a rozšíření
J2 SWD + UART (osadit při ladění). J3 rezervní GPIO, I2C, volné vstupy.

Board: 4 copper layers, 176 parts (5 on the bottom side), 188 nets, no tracks yet.

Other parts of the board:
H1, H2, H3, H4: M3; MountingHole_3.2mm_M3_Pad_Via

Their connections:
GND: H1.1, H2.1, H3.1, H4.1; also elsewhere on the board

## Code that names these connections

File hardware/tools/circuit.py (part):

"""vMix Replay Controller main board: netlist description.

Run gen.py to turn this into KiCad schematic files. Pin assignment and design
notes are in hardware/DESIGN.md; keep both in sync.
"""
from schgen import Part
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    s.add(R("R2", "5.1k", "USB_CC2", "GND"))
    # SRV05-4 (Preferred, bez poplatku) místo USBLC6-2SC6: stejné pouzdro, 4 nezávislé diody, každá datová linka má 2
    s.add(Part("U1", "Power_Protection:SRV05-4", "SRV05-4", "Package_TO_SOT_SMD:SOT-23-6",
               pins={"1": "USB_CONN_DP", "4": "USB_CONN_DP", "3": "USB_CONN_DM", "6": "USB_CONN_DM",
                     "5": "VBUS", "2": "GND"}, lcsc="C7420376", mpn="hongjiacheng SRV05-4"))
    s.add(R("R3", "27R", "USB_CONN_DP", "USB_DP"))
    s.add(R("R4", "27R", "USB_CONN_DM", "USB_DM"))
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    # ABM8-272-T3 (doporučený v Hardware design with RP2040) má JLC skladem 1 ks (12. 11. 2026) -> náhrada se stejnou
    # zatěžovací kapacitou 10 pF, takže obvod (2x 15 pF + 1k) zůstává; ESR max 60 R místo 50 R.
    s.add(Part("Y1", "Device:Crystal_GND24", "12MHz", "Crystal:Crystal_SMD_3225-4Pin_3.2x2.5mm",
               pins={"1": "XIN", "3": "XTAL_OUT", "2": "GND", "4": "GND"}, lcsc="C5310728", mpn="TX322512M4DBDE2T",
               desc="Yajingxin 12 MHz, CL 10 pF, ESR max 60R, +-10 ppm, -30..85 C; pady 1 a 3 krystal, 2 a 4 GND"))
    s.add(R("R10", "1k", "XOUT", "XTAL_OUT"))
    s.add(C("C%d" % n, "15pF", "XIN")); n += 1      # CL 10 pF: 15/2 + ~3 pF parazitní = 10,5 pF (C0G)
    s.add(C("C%d" % n, "15pF", "XTAL_OUT")); n += 1
    s.add(Part("U4", "Memory_Flash:W25Q128JVS", "W25Q128JVSIQ", "Package_SO:SOIC-8_5.3x5.3mm_P1.27mm",
               pins={"1": "QSPI_SS", "2": "QSPI_SD1", "3": "QSPI_SD2", "4": "GND", "5": "QSPI_SD0",
                     "6": "QSPI_SCLK", "7": "QSPI_SD3", "8": "+3V3"}, lcsc="C97521"))
    s.add(C("C%d" % n, "100nF", "+3V3")); n += 1
    s.add(R("R11", "1k", "QSPI_SS", "BOOTSEL"))
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               pins={"1": "BOOTSEL", "2": "GND"}, lcsc="C318884"))
    s.add(R("R12", "10k", "+3V3", "RUN"))
    s.add(Part("SW2", "Switch:SW_Push", "RESET", "Button_Switch_SMD:SW_Push_1P1T_XKB_TS-1187A",
               pins={"1": "RUN", "2": "GND"}, lcsc="C318884"))
    s.add(R("R13", "1k", "STATUS_LED", "STATUS_LED_A"))   # žlutá Vf ~2 V -> ~1,3 mA
    s.add(Part("D3", "Device:LED", "yellow", LED0603, pins={"A": "STATUS_LED_A", "K": "GND"}, lcsc="C89811",
               mpn="NationStar NCD0603Y2"))
    s.add(Part("J2", "Connector_Generic:Conn_01x07", "DEBUG", "Connector_PinHeader_2.54mm:PinHeader_1x07_P2.54mm_Vertical",
               pins={"1": "+3V3", "2": "SWCLK", "3": "SWDIO", "4": "GND", "5": "RUN", "6": "UART_TX", "7": "UART_RX"},
               in_bom=False, desc="SWD + UART debug header (osadit ručně jen při ladění)"))
    exp = {"1": "+5V", "2": "+3V3", "3": "GND", "4": "GND", "5": "GP10", "6": "GP11", "7": "GP22", "8": "GP23",
           "9": "GP24", "10": "GP28", "15": "I2C_SDA", "16": "I2C_SCL"}
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    s = prj.sheet("Ethernet", "ethernet.kicad_sch", "W5500 + RJ45 HR911105A")
    s.note("Analogová část podle referenčního zapojení WIZnet W5500 (33R série, 49,9R terminace, 6,8nF na RX).")
    s.add(Part("U5", "Interface_Ethernet:W5500", "W5500", "Package_QFP:LQFP-48_7x7mm_P0.5mm",
               pins={"AVDD": "+3V3A", "AGND": "GND", "VDD": "+3V3", "GND": "GND", "TXN": "W_TXN", "TXP": "W_TXP",
                     "RXN": "W_RXN", "RXP": "W_RXP", "EXRES1": "W_EXRES", "VBG": None, "TOCAP": "W_TOCAP",
                     "1V2O": "W_1V2O", "RSVD": "GND", "SPDLED": None, "LINKLED": "W_LINKLED", "DUPLED": None,
                     "ACTLED": "W_ACTLED", "XI/CLKIN": "W_XI", "XO": "W_XO", "~{SCS}": "ETH_CS", "SCLK": "ETH_SCK",
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    for i in range(6):
        s.add(C("C%d" % n, "100nF", "+3V3A")); n += 1
    s.add(C("C%d" % n, "100nF", "+3V3")); n += 1
    s.add(C("C%d" % n, "4.7uF", "W_TOCAP")); n += 1
    s.add(C("C%d" % n, "10nF", "W_1V2O")); n += 1
    # EXRES1 12,4k 1 % (Basic neexistuje) = 10k + 2,4k v sérii, obě Basic 1 %
    s.add(R("R20", "10k", "W_EXRES", "W_EXRES_B"))
    s.add(R("R36", "2.4k", "W_EXRES_B", "GND"))
    s.add(Part("Y2", "Device:Crystal_GND24", "25MHz", "Crystal:Crystal_SMD_3225-4Pin_3.2x2.5mm",
               pins={"1": "W_XI", "3": "W_XO", "2": "GND", "4": "GND"}, lcsc="C9006", mpn="X322525MOB4SI (CL 12 pF)"))
    s.add(C("C%d" % n, "18pF", "W_XI")); n += 1    # CL 12 pF: 18/2 + ~3 pF = 12 pF (jako WIZ850io)
    s.add(C("C%d" % n, "18pF", "W_XO")); n += 1
    s.add(R("R21", "1M", "W_XI", "W_XO"))
    s.add(R("R22", "10k", "+3V3", "ETH_INT"))
    s.add(R("R23", "10k", "+3V3", "ETH_RST"))
    s.add(R("R35", "10k", "+3V3", "ETH_CS"))   # W5500 odpojený od SPI, dokud RP2040 nenastaví GPIO
    # TX
    s.add(R("R24", "0R", "W_TXP", "ETH_TDP"))
    s.add(R("R25", "0R", "W_TXN", "ETH_TDN"))
    s.add(R("R26", "49.9R 1%", "ETH_TDP", "+3V3A"))
    s.add(R("R27", "49.9R 1%", "ETH_TDN", "+3V3A"))
    s.add(R("R28", "10R", "+3V3A", "ETH_TCT"))
    s.add(C("C%d" % n, "22nF", "ETH_TCT")); n += 1
    # RX
    s.add(R("R29", "0R", "W_RXP", "ETH_RXP_T"))
    s.add(R("R30", "0R", "W_RXN", "ETH_RXN_T"))
    s.add(R("R31", "49.9R 1%", "ETH_RXP_T", "ETH_RCT"))
    s.add(R("R32", "49.9R 1%", "ETH_RXN_T", "ETH_RCT"))
    s.add(C("C%d" % n, "6.8nF", "ETH_RXP_T", "ETH_RDP")); n += 1
    s.add(C("C%d" % n, "6.8nF", "ETH_RXN_T", "ETH_RDN")); n += 1
    s.add(C("C%d" % n, "10nF", "ETH_RCT")); n += 1
    s.add(C("C56", "10uF", "+3V3"))   # bulk u VDD W5500 (reference WIZnet má 2x 10 uF)
    # LEDs
    # LED anody 12 a 9 na +3V3, katody 11 a 10 přes 330R do W5500 (aktivní v nule, max. 8 mA)
    s.add(R("R33", "330R", "W_LINKLED", "ETH_LINK_K"))
    s.add(R("R34", "330R", "W_ACTLED", "ETH_ACT_K"))
    s.add(Part("J4", "Connector:RJ45_Hanrun_HR911105A_Horizontal", "HR911105A", "Connector_RJ:RJ45_Hanrun_HR911105A_Horizontal",
               pins={"1": "ETH_TDP", "2": "ETH_TDN", "3": "ETH_RDP", "4": "ETH_TCT", "5": "ETH_RCT", "6": "ETH_RDN",
                     "8": "GND", "9": "+3V3", "10": "ETH_ACT_K", "11": "ETH_LINK_K", "12": "+3V3", "SH": "GND"},
               lcsc="C12074", in_bom=False, fields={"Assembly": "ruční pájení"}))
    prj.flag("+3V3A", s.name)
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    s.note("I_MAX = 58,5 x 1,3 V / R_EXT = 16,2 mA pro R_EXT 4,7k. Jas a celkový odběr omezuje firmware.\n"
           "U6 adresa 0x3C (AD=GND), U7 0x3F (AD=VCC). SDB stažený do nuly: LED po startu zhasnuté.")
    for chip, ad in (("U6", "GND"), ("U7", "+5V_LED")):
        pins = {"VCC": "+5V_LED", "GND": "GND", "EP": "GND", "SDA": "I2C_SDA", "SCL": "I2C_SCL",
                "~{SDB}": "LED_SDB", "AD": ad, "R_EXT": "%s_REXT" % chip}
        for k in range(1, 37):
            pins["OUT%d" % k] = None
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    s = prj.sheet("Inputs", "inputs.kicad_sch", "2x TCA9555 expandér")
    s.note("U8 adresa 0x20, U9 0x21. INT (open drain) společný, pull-up R50.")
    for chip, a0 in (("U8", "GND"), ("U9", "+3V3")):
        pins = {"VCC": "+3V3", "GND": "GND", "EPAD": "GND", "SCL": "I2C_SCL", "SDA": "I2C_SDA",
                "~{INT}": "BTN_INT", "A0": a0, "A1": "GND", "A2": "GND"}
        for name, (c, port) in TCA_MAP.items():
            if c == chip:
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
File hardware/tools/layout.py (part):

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    b.term("R7", "2", 0)
    x6, y6, _ = b.pin("R6", "2")
    b.wire((x6, y6 + 1), (x6 + 3, y6 + 1))
    b.label("VSENSE_5V", x6 + 3, y6 + 1, "right")
    d.shunt("C8", *b.P(x6 + 2, y6 + 1), "down", L=g(1))
    # test points
    for i, ref in enumerate(("TP1", "TP2", "TP3", "TP4", "TP5", "TP6", "TP7")):
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    for k in range(30):
        name = "GPIO%d" % k if k < 26 else "GPIO%d/ADC%d" % (k, k - 26)
        b.term(U, name, 2)
    # crystal: XIN/XOUT labels, R10 in series, Y1 with load caps (bottom-left)
    b.term(U, "XIN", 2)
    b.term(U, "XOUT", 2)
    b.h2("R10", 9, 50)
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    b.wire((rx, ry), (rx, ry + 1), (rx + 3, ry + 1))
    b.junction(rx, ry + 1)
    b.wire((rx, ry + 1), (rx - 3, ry + 1))
    b.label("RUN", rx - 3, ry + 1, "left")
    d._mark("R12", "2")
    b.place("SW2", rx + 5, ry + 1, 0, ref_at=(rx + 3, ry - 1.5), val_at=(rx + 3, ry + 3.5))
    sx, sy, _ = b.pin("SW2", "2")
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    for r in ("R31", "R32"):
        b.to_point(r, b.side(r, "right"), gx + 6, gy + 10)
    b.wire((gx + 6, gy + 10), (gx + 8, gy + 10))
    b.label("ETH_RCT", gx + 8, gy + 10, "right")
    b.h2("C53", gx + 3, gy + 14)
    b.h2("C54", gx + 3, gy + 17)
    b.place("R28", gx + 3, gy + 21, 90)
    b.term("R28", b.side("R28", "left"), 0)
    rx, ry, _ = b.pin("R28", b.side("R28", "right"))
    b.wire((rx, ry), (rx + 3, ry))
    b.label("ETH_TCT", rx + 3, ry, "right")
    d._mark("R28", b.side("R28", "right"))
    d.shunt("C52", *b.P(rx + 1, ry), "down", L=g(1))
    b.v2("C55", gx + 14, gy + 23, Lt=1)
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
